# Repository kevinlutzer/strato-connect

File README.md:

# Strato Connect

Strato Connect is an RF module used to send AX.25 formatted data with (G)FSK modulation over I2C. Connect a host MCU or computer to this module, and you can communicate with any AX.25 supported receiver up to 100 kilometers line of sight. 

# Rev 2.0 PCB Todo
1. The current boost regulator doesn't really work. We are getting voltage drops when there are current spikes. 
1. IRQ was not connected.
1. RX/TX labels are wrong for the uart port. 
1. Switch the JST connectors to be the 1.0mm pitch connector type used for QT/QWICC
1. Refactor the code to take an interface in for the I2C Controller instead of passing a function pointer

# Code
To compile and run tests use: `g++ test/test.cpp ax25/ax25.* test/ax25_test.h -lgtest -std=c++17 && ./a.out`
To compile code for arduino use: `arduino-cli compile -b MiniCore:avr:328 --library=./rf4463,./ax25 --output-dir=bin`

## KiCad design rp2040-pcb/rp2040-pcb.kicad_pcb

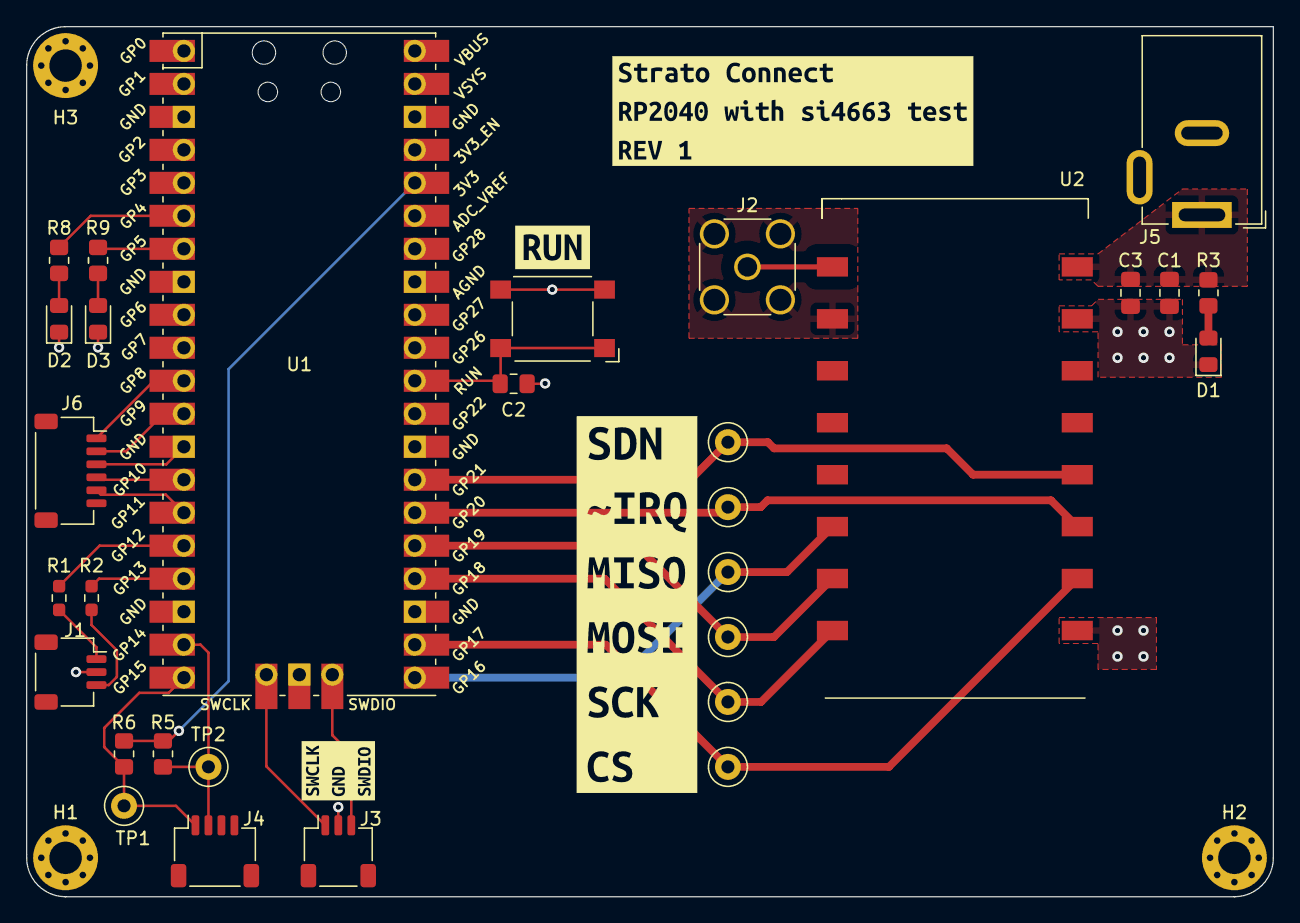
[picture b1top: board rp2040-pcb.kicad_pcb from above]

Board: 2 copper layers, 96.0 x 67.0 mm, 37 parts (0 on the bottom side), 29 nets.

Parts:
C1, C2, C3: C; C_0805_2012Metric_Pad1.18x1.45mm_HandSolder
D1, D2, D3: LED; LED_0805_2012Metric_Pad1.15x1.40mm_HandSolder
H1, H2, H3: MountingHole_Pad; MountingHole_2.5mm_Pad_Via
J1, J3: Conn_01x03_Pin; JST_SH_SM03B-SRSS-TB_1x03-1MP_P1.00mm_Horizontal
J2: Conn_Coaxial; SMA_Wurth_60312002114503_Vertical
J4: Conn_01x04_Pin; JST_SH_SM04B-SRSS-TB_1x04-1MP_P1.00mm_Horizontal
J5: Barrel_Jack; BarrelJack_GCT_DCJ200-10-A_Horizontal
J6: Conn_01x06_Socket; JST_SH_SM06B-SRSS-TB_1x06-1MP_P1.00mm_Horizontal
R1, R2: 100; R_0603_1608Metric_Pad0.98x0.95mm_HandSolder
R3, R8, R9: 220; R_0805_2012Metric_Pad1.20x1.40mm_HandSolder
R5, R6: 2k2; R_0805_2012Metric_Pad1.20x1.40mm_HandSolder
SW1: SW_SPST; SW_SPST_Omron_B3FS-100xP
TP1, TP2, TP3, TP4, TP5, TP6, TP7, TP8: TestPoint; TestPoint_Loop_D1.80mm_Drill1.0mm_Beaded
U1: Pico; RPi_Pico_SMD_TH
U2: RF4463F30
kibuzzard-654DA23D: G***; kibuzzard-654DA23D
kibuzzard-654DA24D: G***; kibuzzard-654DA24D
kibuzzard-654DAC3C: G***; kibuzzard-654DAC3C
kibuzzard-654DC7E1: G***; kibuzzard-654DC7E1

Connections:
+3V3: R5.2, R6.2, U1.36 (3V3)
+VDC: C1.1, C3.1, J5.1, R3.1, U2.16 (VCC)
/RF_GND: J2.2 (Ext), U2.2 (ANT_GND)
GND: C1.2, C2.2, C3.2, D1.1 (K), D2.1 (K), D3.1 (K), H1.1, H2.1, H3.1, J1.2, J3.2, J4.4, J5.2, J6.3, SW1.2 (B), U1.3 (GND), U1.8 (GND), U1.13 (GND), U1.18 (GND), U1.23 (GND), U1.28 (GND), U1.33 (AGND), U1.38 (GND), U1.42 (GND), U2.9 (GND), U2.15 (GND)
I2C_SCL: J4.1, R6.1, TP1.1, U1.20 (GPIO15)
I2C_SDA: J4.2, R5.1, TP2.1, U1.19 (GPIO14)
LED1: R8.1, U1.6 (GPIO4)
LED2: R9.1, U1.7 (GPIO5)
unnamed: D1.2 (A), R3.2
unnamed: D2.2 (A), R8.2
unnamed: D3.2 (A), R9.2
unnamed: J1.1, R1.1
unnamed: J1.3, R2.1
unnamed: J2.1 (In), U2.1 (ANT)
RUN: C2.1, SW1.1 (A), U1.30 (RUN)
SDN: TP8.1, U1.27 (GPIO21), U2.12 (SDN)
SPI0_MISO: TP3.1, U1.21 (GPIO16), U2.6 (SDO)
SPI0_MOSI: TP4.1, U1.25 (GPIO19), U2.7 (SDI)
SPI0_SCK: TP5.1, U1.24 (GPIO18), U2.8 (SCLK)
SPI1_MISO: J6.1, U1.11 (GPIO8)
SPI1_MOSI: J6.5, U1.15 (GPIO11)
SPI1_SCK: J6.4, U1.14 (GPIO10)
SWCLK: J3.1, U1.41 (SWCLK)
SWDIO: J3.3, U1.43 (SWDIO)
UART_RX: R2.2, U1.17 (GPIO13)
UART_TX: R1.2, U1.16 (GPIO12)
~IRQ: TP7.1, U1.26 (GPIO20), U2.11 (~IRQ)
~SPI0_CS: TP6.1, U1.22 (GPIO17), U2.10 (~SEL)
~SPI1_CS: J6.2, U1.12 (GPIO9)

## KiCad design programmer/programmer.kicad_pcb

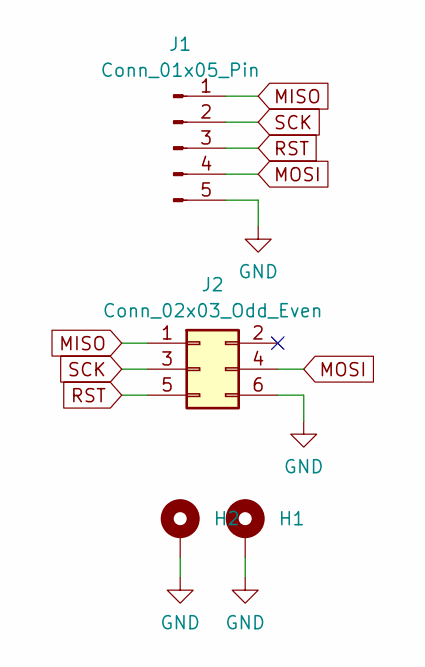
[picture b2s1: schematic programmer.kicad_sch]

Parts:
H1, H2: MountingHole_Pad; MountingHole_3mm_Pad_Via
J1: Conn_01x05_Pin; PinHeader_1x05_P2.54mm_Vertical
J2: Conn_02x03_Odd_Even; PinHeader_2x03_P2.54mm_Vertical

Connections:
GND: H1.1, H2.1, J1.5, J2.6
MISO: J1.1, J2.1
MOSI: J1.4, J2.4
RST: J1.3, J2.5
SCK: J1.2, J2.3

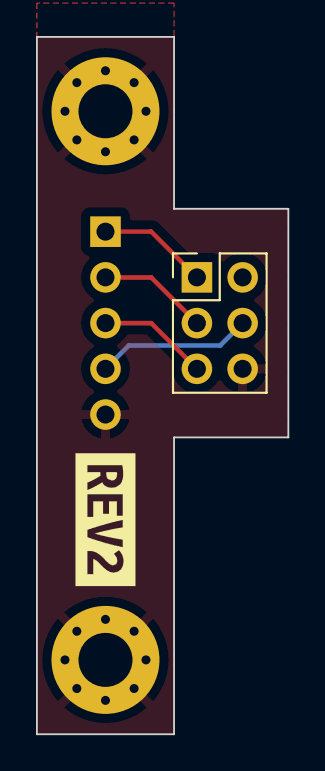
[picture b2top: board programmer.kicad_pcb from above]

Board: 2 copper layers, 14.0 x 38.7 mm, 5 parts (1 on the bottom side), 5 nets.

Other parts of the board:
kibuzzard-64ED132C: G***; kibuzzard-64ED132C

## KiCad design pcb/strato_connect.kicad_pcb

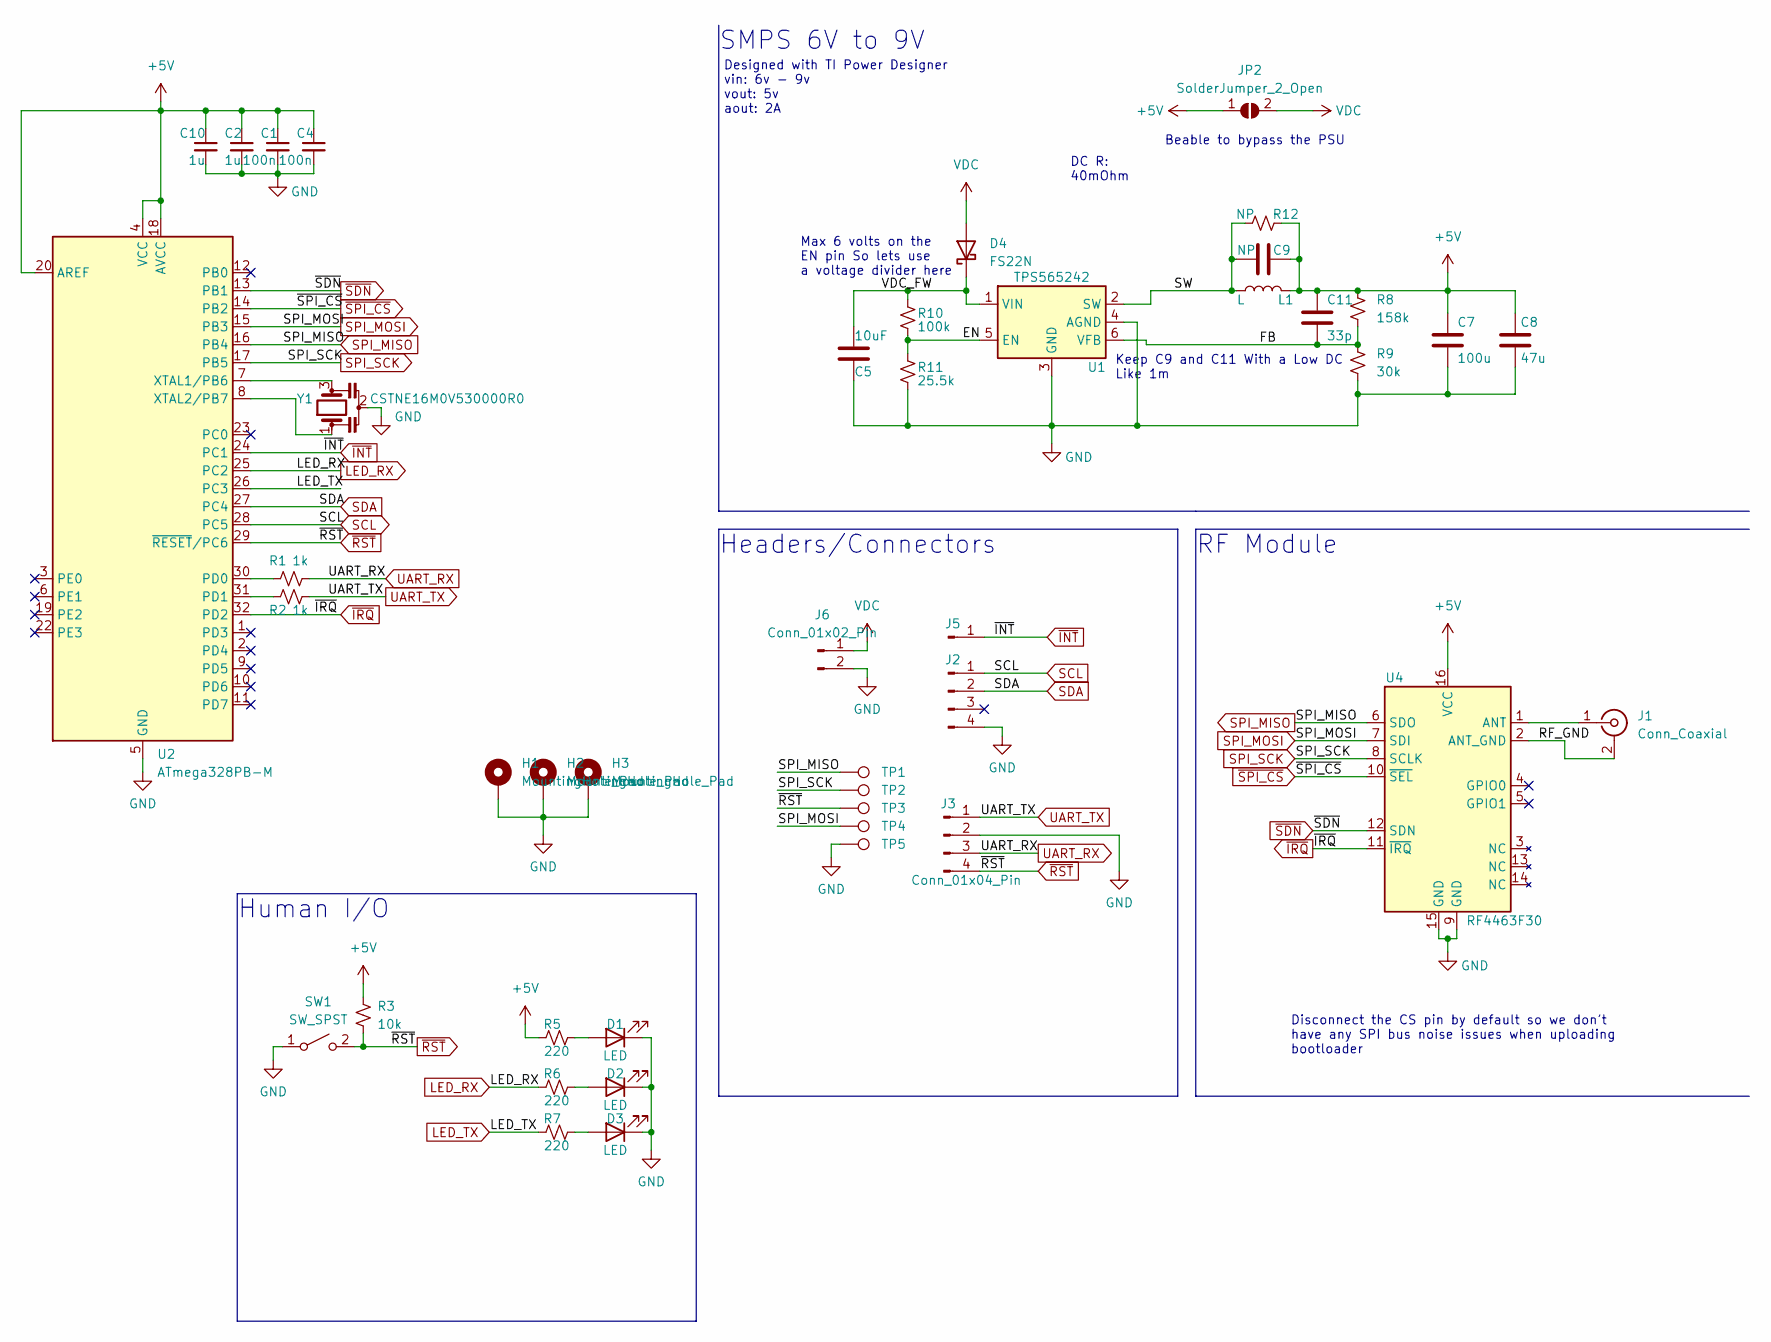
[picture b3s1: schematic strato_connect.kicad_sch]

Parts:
C1, C4: 100n; C_0402_1005Metric_Pad0.74x0.62mm_HandSolder
C2, C10: 1u; C_0402_1005Metric_Pad0.74x0.62mm_HandSolder
C5: 10uF; C_0603_1608Metric_Pad1.08x0.95mm_HandSolder
C7: 100u; CP_Elec_5x5.3
C8: 47u; CP_Elec_5x5.3
C9: NP; C_0402_1005Metric_Pad0.74x0.62mm_HandSolder
C11: 33p; C_0402_1005Metric_Pad0.74x0.62mm_HandSolder
D1, D2, D3: LED; LED_0603_1608Metric
D4: FS22N; D_SOD-123F
H1, H2, H3: MountingHole_Pad; MountingHole_3.2mm_M3_Pad_Via
J1: Conn_Coaxial; SMA_Wurth_60312002114503_Vertical
J2, J3: Conn_01x04_Pin; JST_SH_SM04B-SRSS-TB_1x04-1MP_P1.00mm_Horizontal
J5: Conn_01x01_Pin; TestPoint_Keystone_5019_Minature
J6: Conn_01x02_Pin; JST_PH_S2B-PH-SM4-TB_1x02-1MP_P2.00mm_Horizontal
JP2: SolderJumper_2_Open; SolderJumper-2_P1.3mm_Open_RoundedPad1.0x1.5mm
L1: L; L_Wurth_WE-LQSH-4025
R1, R2: 1k; R_0402_1005Metric_Pad0.72x0.64mm_HandSolder
R3: 10k; R_0402_1005Metric_Pad0.72x0.64mm_HandSolder
R5: 220; R_0603_1608Metric_Pad0.98x0.95mm_HandSolder
R6, R7: 220; R_0402_1005Metric_Pad0.72x0.64mm_HandSolder
R8: 158k; R_0402_1005Metric_Pad0.72x0.64mm_HandSolder
R9: 30k; R_0402_1005Metric_Pad0.72x0.64mm_HandSolder
R10: 100k; R_0402_1005Metric_Pad0.72x0.64mm_HandSolder
R11: 25.5k; R_0402_1005Metric_Pad0.72x0.64mm_HandSolder
R12: NP; R_0402_1005Metric_Pad0.72x0.64mm_HandSolder
SW1: SW_SPST; SW_Push_1P1T_NO_CK_KMR2
TP1, TP2, TP3, TP4, TP5: TestPoint; TestPoint_THTPad_D1.0mm_Drill0.5mm
U1: TPS565242; SOT-563
U2: ATmega328PB-M; QFN-32-1EP_5x5mm_P0.5mm_EP3.1x3.1mm
U4: RF4463F30
Y1: CSTNE16M0V530000R0; Resonator_SMD_Murata_CSTxExxV-3Pin_3.0x1.1mm

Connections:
+5V: C1.1, C2.1, C4.1, C7.1, C8.1, C9.1, C10.1, C11.1, JP2.1 (A), L1.2, R3.1, R5.1, R8.1, R12.2, U2.4 (VCC), U2.18 (AVCC), U2.20 (AREF), U4.16 (VCC)
/EN: R10.2, R11.1, U1.5 (EN)
/FB: C11.2, R8.2, R9.1, U1.6 (VFB)
/RF_GND: J1.2 (Ext), U4.2 (ANT_GND)
/SW: C9.2, L1.1, R12.1, U1.2 (SW)
/VDC_FW: C5.1, D4.1 (K), R10.1, U1.1 (VIN)
GND: C1.2, C2.2, C4.2, C5.2, C7.2, C8.2, C10.2, D1.1 (K), D2.1 (K), D3.1 (K), H1.1, H2.1, H3.1, J2.4, J3.2, J6.2, R9.2, R11.2, SW1.1 (A), TP5.1, U1.3 (GND), U1.4 (AGND), U2.5 (GND), U2.21 (GND), U2.33 (GND), U4.9 (GND), U4.15 (GND), Y1.2
LED_RX: R6.1, U2.25 (PC2)
LED_TX: R7.1, U2.26 (PC3)
unnamed: D1.2 (A), R5.2
unnamed: D2.2 (A), R6.2
unnamed: D3.2 (A), R7.2
unnamed: J1.1 (In), U4.1 (ANT)
unnamed: R1.1, U2.30 (PD0)
unnamed: R2.1, U2.31 (PD1)
unnamed: U2.7 (XTAL1/PB6), Y1.3
unnamed: U2.8 (XTAL2/PB7), Y1.1
SCL: J2.1, U2.28 (PC5)
SDA: J2.2, U2.27 (PC4)
SPI_MISO: TP1.1, U2.16 (PB4), U4.6 (SDO)
SPI_MOSI: TP4.1, U2.15 (PB3), U4.7 (SDI)
SPI_SCK: TP2.1, U2.17 (PB5), U4.8 (SCLK)
UART_RX: J3.3, R1.2
UART_TX: J3.1, R2.2
VDC: D4.2 (A), J6.1, JP2.2 (B)
~INT: J5.1, U2.24 (PC1)
~IRQ: U2.32 (PD2), U4.11 (~IRQ)
~RST: J3.4, R3.2, SW1.2 (B), TP3.1, U2.29 (~RESET/PC6)
~SDN: U2.13 (PB1), U4.12 (SDN)
~SPI_CS: U2.14 (PB2), U4.10 (~SEL)

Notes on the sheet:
Headers/Connectors
Human I/O
DC R: 40mOhm
SMPS 6V to 9V
Max 6 volts on the EN pin So lets use a voltage divider here
Keep C9 and C11 With a Low DC Like 1m
Designed with TI Power Designer vin: 6v - 9v vout: 5v aout: 2A
RF Module
Disconnect the CS pin by default so we don't have any SPI bus noise issues when uploading bootloader
Beable to bypass the PSU

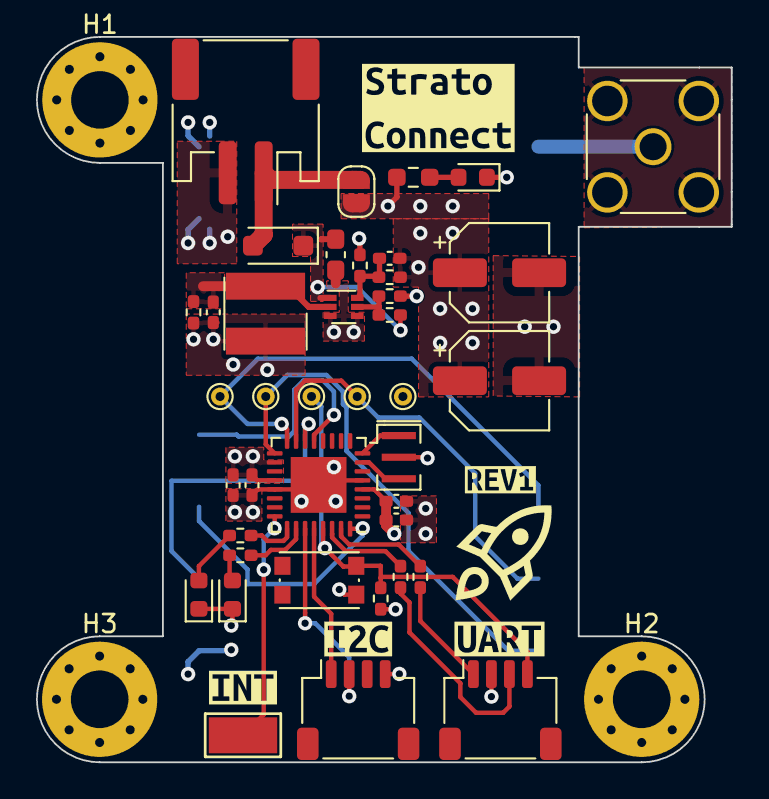
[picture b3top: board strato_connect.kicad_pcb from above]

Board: 4 copper layers, 38.6 x 40.3 mm, 49 parts (1 on the bottom side), 30 nets.

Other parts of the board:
kibuzzard-64B1A87B: G***; kibuzzard-64B1A87B
kibuzzard-64B1A828: G***; kibuzzard-64B1A828
kibuzzard-64B1A895: G***; kibuzzard-64B1A895
kibuzzard-64B1B5E1: G***; kibuzzard-64B1B5E1
kibuzzard-64B1B6FD: G***; kibuzzard-64B1B6FD

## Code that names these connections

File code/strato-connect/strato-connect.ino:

#include "rf4463.hpp"
#include "ax25.hpp"
#include "i2ccontroller.hpp"
#include <SPI.h>
#include <Wire.h>

#define IRQ 2
#define SDN 9
#define SEL 10
#define SCL 19

#define LED_RX 16
#define LED_TX 17
#define INT 15

AX25 ax25 = AX25();
RF4463 rf4463 = RF4463(IRQ, SDN, SEL);
I2CController i2ccontroller = I2CController(&ax25, &Wire);
unsigned char tx_buf[]={"NEW HELLO WORLD!!!"};
unsigned char val;
unsigned char flag=0;    //  flag of rx mode
unsigned char rx_len;
unsigned char rx_buf[20];

void setup() {
  Serial.begin(9600);

  pinMode(LED_RX, OUTPUT);
  pinMode(LED_TX, OUTPUT);
  pinMode(INT, OUTPUT);

  digitalWrite(LED_RX, HIGH);
  digitalWrite(LED_RX, HIGH);
  digitalWrite(INT, HIGH);

  while(true) {
    Serial.println("Waiting for serial...");
    delay(1000);
  }

  if(!rf4463.init())
    Serial.println("Init fail!");
  else
    Serial.println("Init success!");

  if(!rf4463.setTxPower(127))
    Serial.println("Failed to set power to max!");
}

void loop() {
  rf4463.txPacket(tx_buf,sizeof(tx_buf));
  delay(1000);
}

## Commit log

2023-05-25 add base pcb with crystal, reset switch and bypassing caps
2023-05-26 draw out the base schematic with the RF module
2023-05-31 add rough margin
2023-06-10 finish the shcematic, need to adjust component packages for headers, inductors and some of the resistors
2023-06-10 add some more annotations to the smps
2023-06-10 add 6060 Inductor foodprint
2023-06-10 build out the VQFN7-7 footbring for the boost converter
2023-06-11 update schematic to add mroe room for the smps
2023-06-12 finish routing the smps, need to extend the footprint pads for the rf module
2023-06-13 add some of the header labels we need. Finish routing everything but uart, the iscp header, and some other small stuff
2023-06-15 finish the design
2023-06-15 add gerbers
2023-06-19 add bom, readjust capactor annotations
2023-06-19 more adjustments
2023-06-28 add notes about the v2 version of the pcb
2023-07-02 add labels update rf lib
2023-07-03 remove the i2c level shifter, add the TPS565 smps chip
2023-07-03 fix all the erc warnings
2023-07-07 rename the schematic
2023-07-07 rough layout of the rev2 pcb
2023-07-13 get most of the layout done, need to add some sort of icsp header pins
2023-07-14 pass DRC with the schematic capture
2023-07-14 add the 4025 Weurth inductor footprint in
2023-07-14 pass drc rules for files, just have to add the silk screen
2023-07-14 Switch the coax connector type
2023-08-01 add v2 files for the pcb, add the base code directory
2023-08-04 get the apply callsign method working
2023-08-06 add the ax25 base code and tests
2023-08-08 move test file into test direectory
2023-08-08 add the .gitignore
2023-08-09 rename to cpp/hpp files
2023-08-23 use a fixed frame init
2023-08-23 bring in another library to compare
2023-08-24 WIP Before Revert
2023-08-24 get the base encode fucntion to work
2023-08-24 leds
2023-08-25 add the base i2c controller with a ping handler
2023-08-25 comment out tests to make everything pass
2023-08-26 add tests for the i2c controller and mocks
2023-08-26 i2c controller constructor talking two wire instance
2023-08-26 get tests to pass with mock instance
2023-08-26 try and add the ping method
2023-08-26 tests pass
2023-08-27 start building out the controller with semi working tests and mocks
2023-08-28 update programming pcb so it can be secured to the stemma grid
2023-10-11 update documentation
2023-11-10 add the rp2040/si4663 test pcb
2025-09-01 convert to platform I/O
